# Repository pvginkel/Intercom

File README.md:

# TODO

- BLink lights during startup.
- Blink lights on failure.

# Pin assignment

PB = purple = 33
LR = orange = 18
LG = orange = 17

Speaker

LRC = green = 13
BCLK = blue = 14
SDI = yellow = 15

Microphone

WS = green = 35
SCK = blue = 36
SDO = yellow = 37

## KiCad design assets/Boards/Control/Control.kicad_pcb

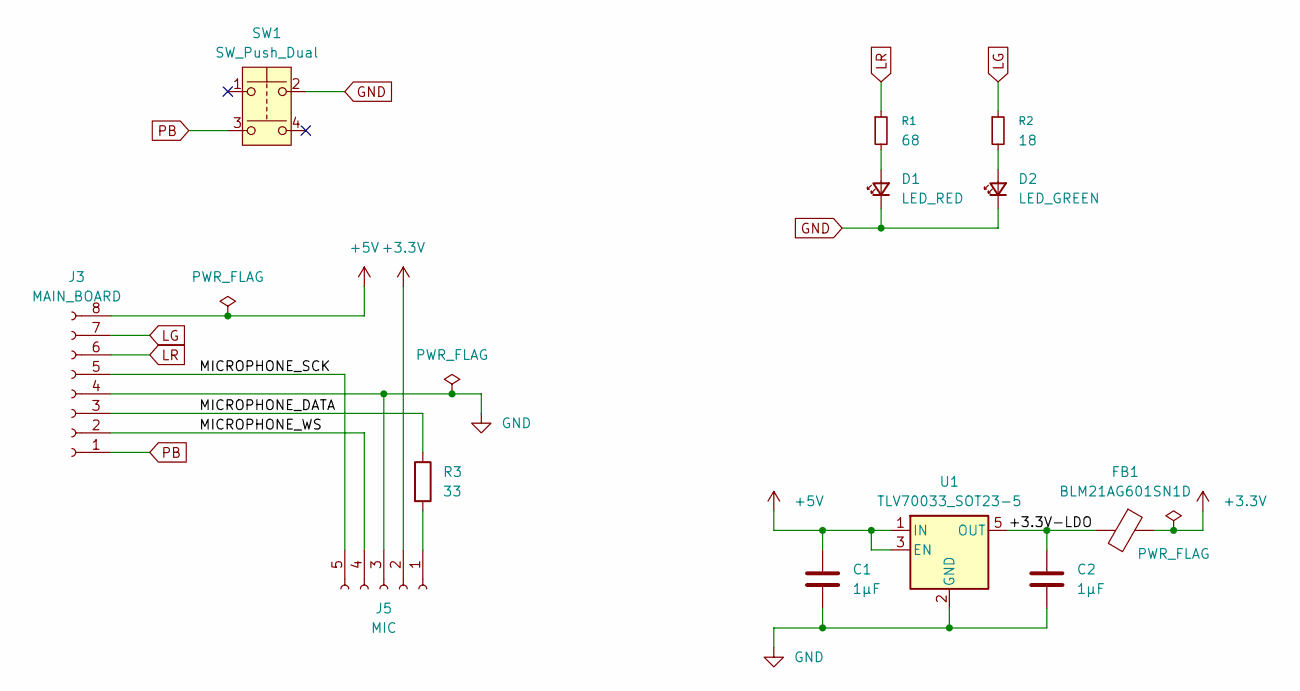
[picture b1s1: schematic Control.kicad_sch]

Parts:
C1, C2: 1µF; C_0805_2012Metric_Pad1.18x1.45mm_HandSolder
D1: LED_RED; LED_D5.0mm_Clear
D2: LED_GREEN; LED_D5.0mm_Clear
FB1: BLM21AG601SN1D; L_0805_2012Metric_Pad1.15x1.40mm_HandSolder
J3: MAIN_BOARD; JST_PH_S8B-PH-K_1x08_P2.00mm_Horizontal
J5: MIC; JST_PH_S5B-PH-K_1x05_P2.00mm_Horizontal
R1: 68; R_0805_2012Metric_Pad1.20x1.40mm_HandSolder
R2: 18; R_0805_2012Metric_Pad1.20x1.40mm_HandSolder
R3: 33; R_0805_2012Metric_Pad1.20x1.40mm_HandSolder
SW1: SW_Push_Dual; Pushbutton 12x12x7.3
U1: TLV70033_SOT23-5; SOT-23-5

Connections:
+3.3V: FB1.1, J5.2
+5V: C1.2, J3.8, U1.1 (IN), U1.3 (EN)
/+3.3V-LDO: C2.1, FB1.2, U1.5 (OUT)
/MICROPHONE_DATA: J3.3, R3.1
/MICROPHONE_SCK: J3.5, J5.5
/MICROPHONE_WS: J3.2, J5.4
GND: C1.1, C2.2, D1.1 (K), D2.1 (K), J3.4, J5.3, SW1.2, U1.2 (GND)
LG: J3.7, R2.1
LR: J3.6, R1.1
unnamed: D1.2 (A), R1.2
unnamed: D2.2 (A), R2.2
unnamed: J5.1, R3.2
PB: J3.1, SW1.3

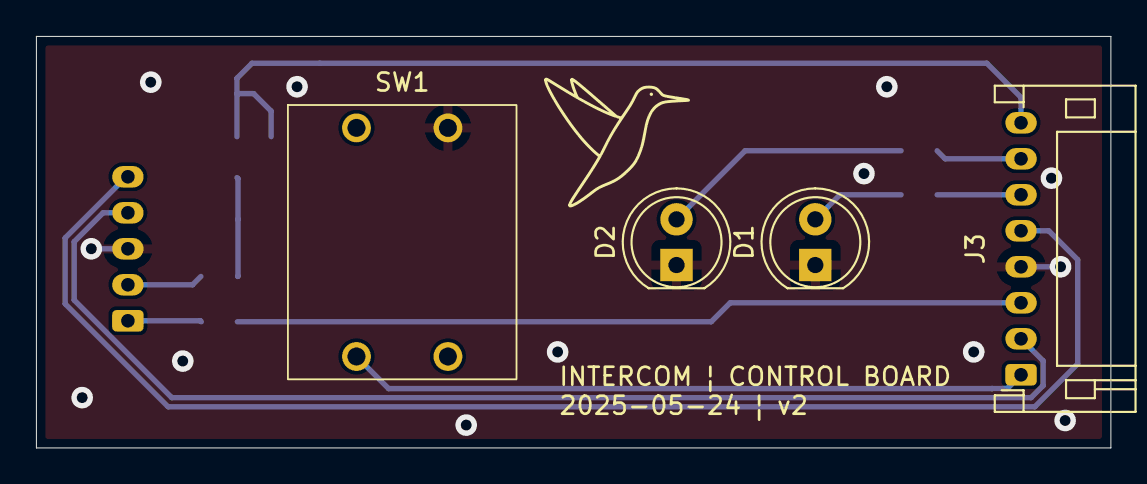
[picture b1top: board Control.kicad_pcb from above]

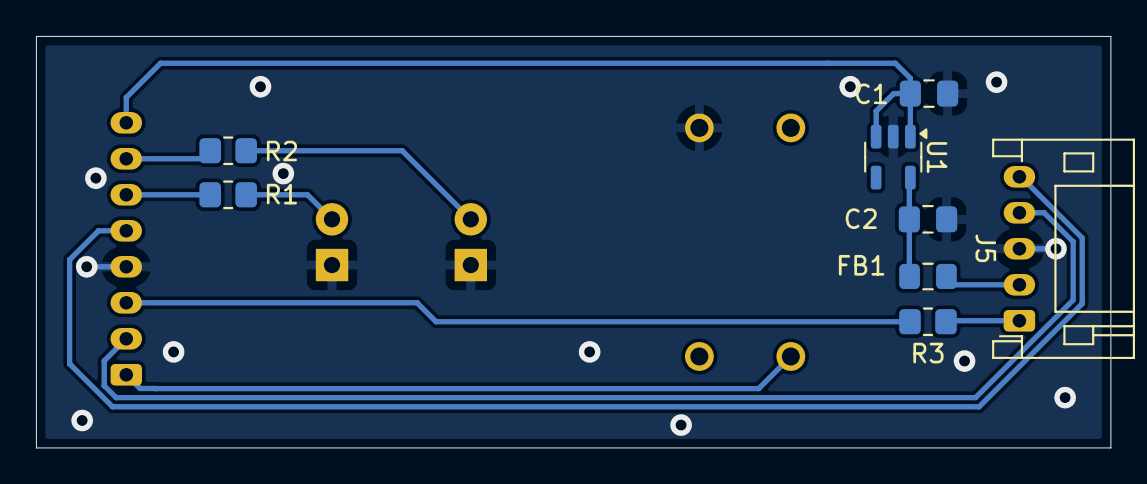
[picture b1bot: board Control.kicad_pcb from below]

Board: 2 copper layers, 59.7 x 22.9 mm, 12 parts (8 on the bottom side), 13 nets.

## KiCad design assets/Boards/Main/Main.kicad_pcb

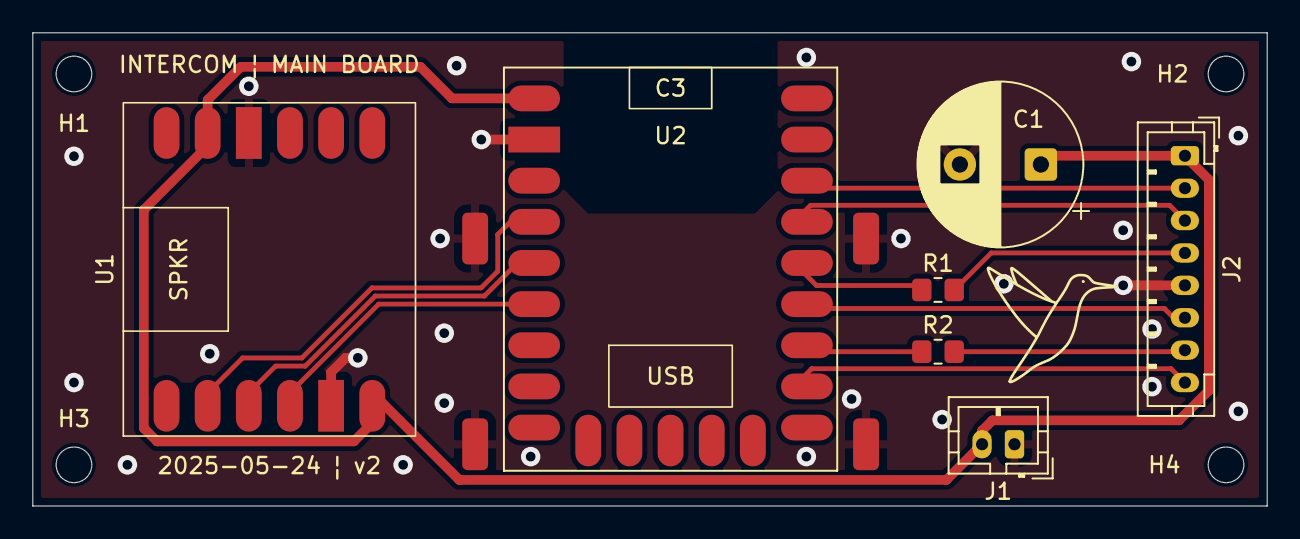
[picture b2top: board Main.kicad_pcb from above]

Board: 2 copper layers, 76.2 x 29.2 mm, 15 parts (0 on the bottom side), 13 nets.

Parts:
C1: 1000 µF; CP_Radial_D10.0mm_P5.00mm
H1, H2, H3, H4: MountingHole; MountingHole_2.2mm_M2_DIN965
J1: PWR; JST_PH_B2B-PH-K_1x02_P2.00mm_Vertical
J2: CTRLS_BOARD; JST_PH_B8B-PH-K_1x08_P2.00mm_Vertical
R1, R2: 33; R_0805_2012Metric_Pad1.20x1.40mm_HandSolder
U1: DFRobot_MAX98357; DFRobot_MAX98357_SMD
U2: Waveshare_ESP32-S3-Tiny; Waveshare_ESP32-S3-Tiny_SMD
U3, U4, U5, U8: Solder pad 1.6x3.3mm

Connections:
+5V: C1.1, J1.2, J2.1, U1.6 (VCC1), U1.11 (VCC2), U2.1 (5V)
GND: C1.2, J1.1, J2.5, U1.5 (GND1), U1.10 (GND2), U2.2 (G), U3.1, U4.1, U5.1, U8.1
LG: J2.2, U2.21 (18)
LR: J2.3, U2.20 (17)
MICROPHONE_DATA: J2.6, U2.18 (15)
MICROPHONE_SCK: J2.4, R1.2
MICROPHONE_WS: J2.7, R2.2
unnamed: R2.1, U2.17 (14)
unnamed: R1.1, U2.19 (16)
PB: J2.8, U2.16 (13)
SPEAKER_DATA: U1.2 (DIN), U2.4 (1)
SPEAKER_SCK: U1.3 (BCLK), U2.5 (2)
SPEAKER_WS: U1.4 (LRC), U2.6 (3)

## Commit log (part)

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2025-02-15 Added 3D models.
2025-03-16 Initial ESP-IDF project commit.
2025-03-16 Got the controls to work.
2025-03-16 Got the speaker to work (somewhat).
2025-03-19 Minor improvement.
2025-03-22 Got a minimally functional device to work.
2025-03-28 Refactoring.
2025-03-28 Updated INMP441 implementation.
    See https://github.com/pvginkel/INMP441Test for more information.
2025-03-28 Cleanup.
2025-03-28 Feed reference channel to AFE.
2025-04-13 Added PCB board.
2025-04-13 Show CPU statistics.
2025-04-13 Reconfigured for the real PCB board.
2025-04-13 Stream audio over UDP, fixed AEC.
2025-04-19 Remove the need for a model partition.
2025-04-19 Set bootstrapper OTA endpoint.
2025-04-19 Add script to upload OTA binary.
2025-04-20 Removed support for the bootstrapper app.
2025-04-27 Implemented volume control.
2025-04-27 Rotated capacitor.
2025-04-28 Moved MQTT configuration into the device configuration file.
2025-04-30 Added build script.
2025-04-30 Simplified upload script.
2025-05-01 Fade led on startup.
2025-05-01 Implemented identify.
2025-05-01 Reworked copying esp-libs projects.
2025-05-02 Minor fixes to improve MQTT startup sequence.
2025-05-03 Minor improvements to EAC.
2025-05-03 Use volume offset instead of target Db as volume control.
2025-05-03 Changed the default volume.
2025-05-03 Added support for restart and getting firmware version.
2025-05-03 Publish MQTT discovery metadata.
2025-05-04 Improved MQTT discovery.
2025-05-09 Ensure memory in the read task is internal memory.
2025-05-11 Improved audio quality.
2025-05-11 Improved NVS handling of the device.
2025-05-11 Fixed MQTT discovery metadata.
2025-05-14 Set max WiFi transmission power.
2025-05-14 Updated WiFi defaults to correspond to the ESP32-S3 Tiny SOC.
2025-05-18 Added ground plane, RF shield soldering points and text.
2025-05-22 Reworked boards.
    Added LDO for the mic. Changed layout of the main board to move the cap out of the way. Added ground and power plane. Added R33's for the signal lines of the mic.
2025-05-23 Fixed ERC errors. Switched to double ground plane instead of ground and power plane. Switched to 1uF caps for the LDO conforming to the data sheet. Added logo.
2025-05-24 Applied suggestions from Rick Hartley.
    See https://www.youtube.com/watch?v=ySuUZEjARPY.
2025-05-24 Applied suggestions from people from the KiCad forum.
2026-05-27 Integrated Intercom with the new MDM system.
2026-05-27 Added PowerShell upload script.
2026-05-27 Removed unnecessary clone of HelmCharts.
2026-05-27 Added missing IoTSupport secrets to allow the firmware to be pushed to MDM.
2026-06-02 Fixed ESP-IDF path.
2026-06-02 Updated boards.
2026-06-02 Untrack sdkconfig.
2026-06-02 Migrated the app to the new MDM software.
2026-06-02 Create storage NVM when missing.
2026-06-02 Ignore cache folder.
2026-06-02 Simplified pipeline.
2026-06-02 Fixed ESP-IDF container version.
2026-06-02 Minor fix.
2026-06-02 Pin IDF target.
2026-06-04 Implemented support for multiple hardware versions.
2026-06-04 Jenkinsfile: load JenkinsPipelineUtils with changelog:false
    Use the `library identifier: ..., changelog: false` form so pushes to
    the shared JenkinsPipelineUtils library no longer trigger this job via
    SCM polling.
2026-06-05 Vary WiFi TX power per hardware version.
2026-06-05 Removed obsolete secrets generation.
2026-06-05 Throttle error messages from UDPServer.
2026-06-05 Added script to generate discovery messages to test the ACK system.
2026-06-07 Fixed MQTT discovery publication.
